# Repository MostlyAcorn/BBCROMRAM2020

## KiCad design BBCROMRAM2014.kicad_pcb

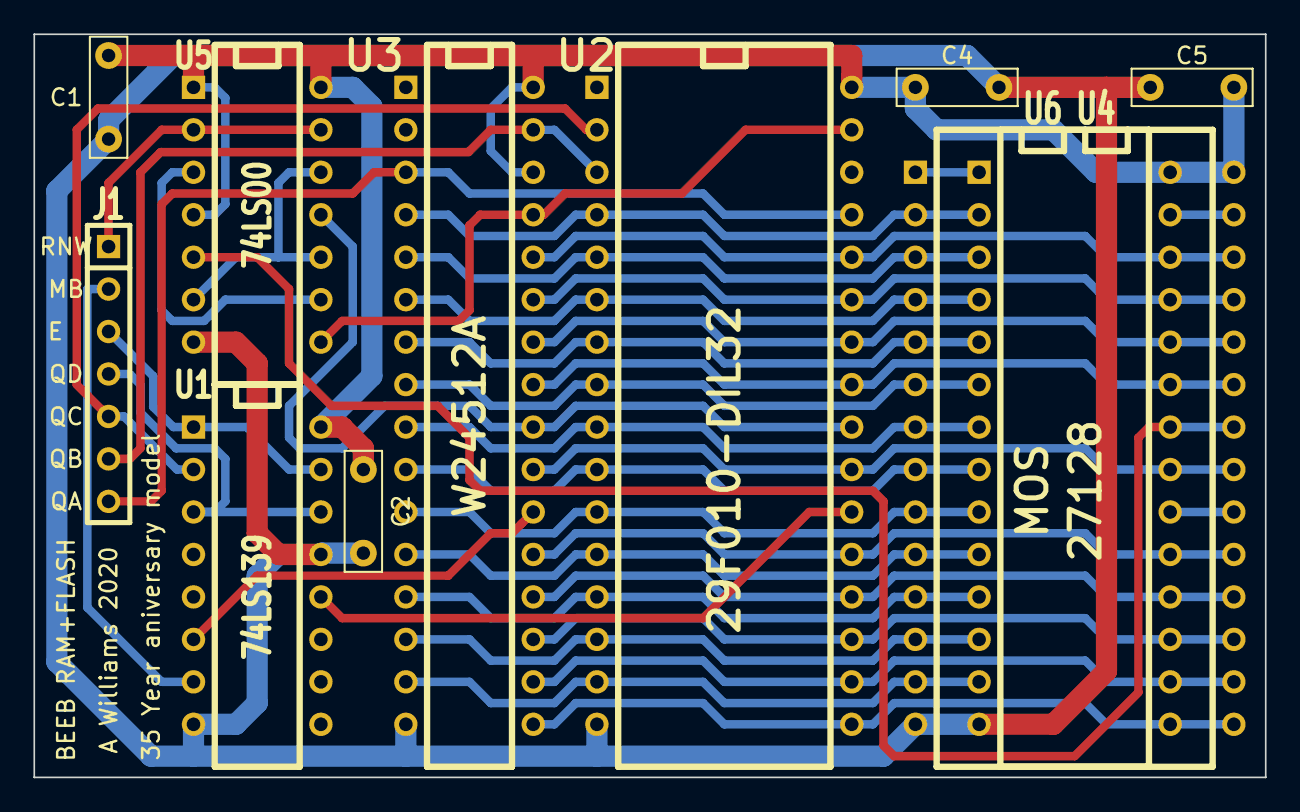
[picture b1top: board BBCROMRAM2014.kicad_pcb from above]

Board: 2 copper layers, 73.7 x 44.4 mm, 11 parts (0 on the bottom side), 41 nets.

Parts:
C1, C2, C4, C5: 0.1uF; C_Rect_L7.0mm_W2.0mm_P5.00mm
J1: CON1; SIL-7
U1: 74LS139; DIP-16__300
U2: 29F010-DIL32; DIP-32__600
U3: W24512A; DIP-32__300
U4: MOS; DIP-28__600
U5: 74LS00; DIP-14__300
U6: 27128; DIP-28__600

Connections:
/A0: U2.12, U3.12, U4.10, U6.10
/A1: U2.11, U3.11, U4.9, U6.9
/A2: U2.10, U3.10, U4.8, U6.8
/A3: U2.9, U3.9, U4.7, U6.7
/A4: U2.8, U3.8, U4.6, U6.6
/A5: U2.7, U3.7, U4.5, U6.5
/A6: U2.6, U3.6, U4.4, U6.4
/A7: U2.5, U3.5, U4.3, U6.3
/A8: U2.27, U3.27, U4.25, U6.25
/A9: U2.26, U3.26, U4.24, U6.24
/A10: U2.23, U3.23, U4.21, U6.21
/A11: U2.25, U3.25, U4.23, U6.23
/A12: U2.4, U3.4, U4.2, U6.2
/A13: U2.28, U3.28, U4.26, U6.26
/D0: U2.13, U3.13, U4.11, U6.11
/D1: U2.14, U3.14, U4.12, U6.12
/D2: U2.15, U3.15, U4.13, U6.13
/D3: U2.17, U3.17, U4.15, U6.15
/D4: U2.18, U3.18, U4.16, U6.16
/D5: U2.19, U3.19, U4.17, U6.17
/D6: U2.20, U3.20, U4.18, U6.18
/D7: U2.21, U3.21, U4.19, U6.19
/E: J1.3, U1.1, U1.15
/MB: J1.2, U1.7
/MCE: U4.20, U6.20
/MOE: U4.22, U5.5, U6.22
/MPGM: U4.27, U6.27
/MVPP: U4.1, U6.1
/NFLASHCS: U1.12, U2.22
/NOE: U2.24, U3.24, U5.11
/NRAMCS: U1.6, U3.22
/NWDS: U2.31, U3.29, U5.8
/QA: J1.7, U2.29, U3.3
/QB: J1.6, U2.3, U3.31
/QC: J1.5, U1.2, U2.2
/QD: J1.4, U1.3, U1.14
/RNW: J1.1, U5.2, U5.13
GND: C1.2, C2.2, C4.2, C5.2, U1.8, U1.13, U2.16, U3.16, U4.14, U5.7, U6.14
unnamed: U5.3, U5.9
unnamed: U5.6, U5.10, U5.12
VCC: C1.1, C2.1, C4.1, C5.1, U1.16, U2.32, U3.30, U3.32, U4.28, U5.1, U5.4, U5.14, U6.28
